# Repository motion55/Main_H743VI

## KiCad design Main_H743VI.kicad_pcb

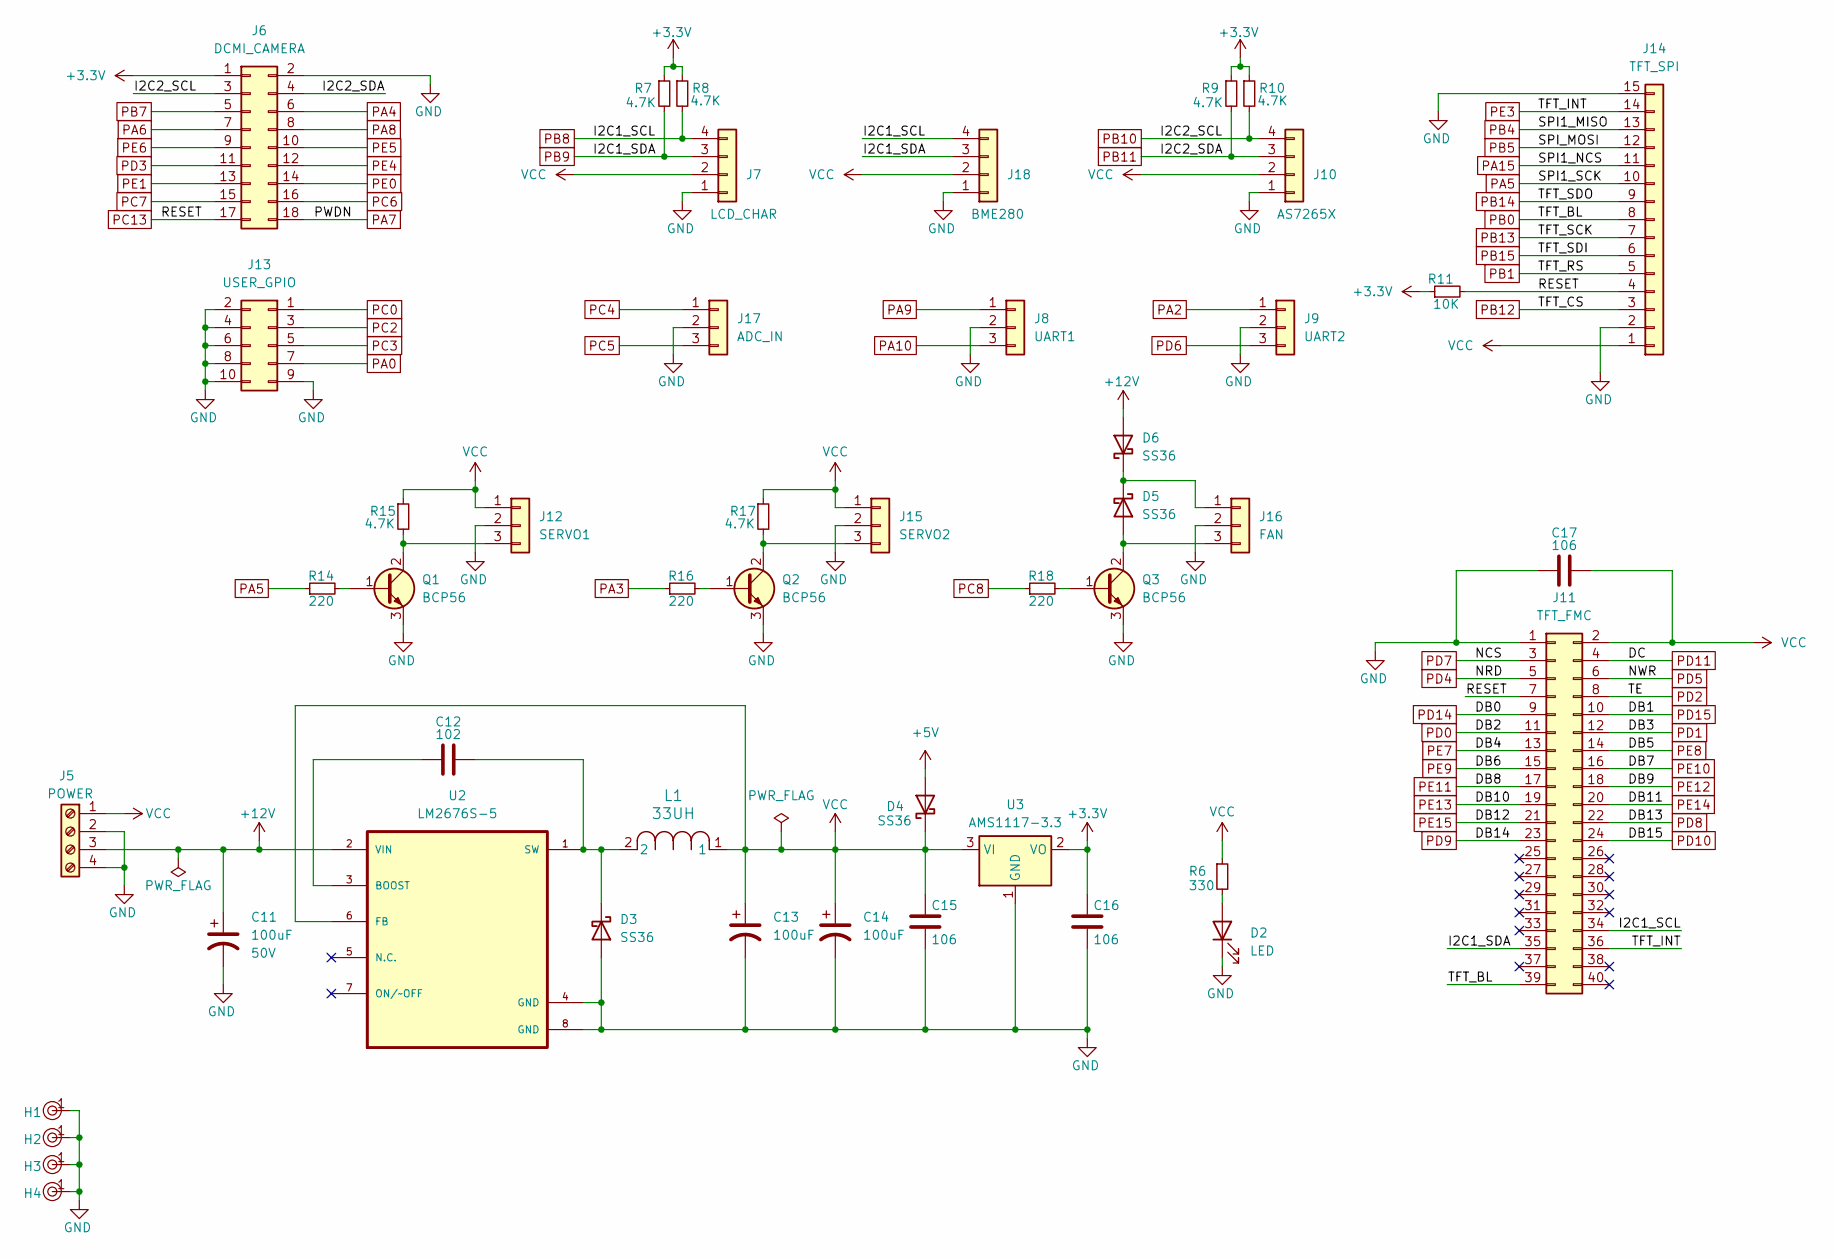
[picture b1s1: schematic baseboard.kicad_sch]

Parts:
C11: 100uF; CP_Radial_D8.0mm_P5.00mm; Tolerance 100%; Voltage 50V
C12: 102; C_0603_1608Metric_Pad1.08x0.95mm_HandSolder
C13, C14: 100uF; CP_Radial_D8.0mm_P5.00mm
C15, C16, C17: 106; C_0805_2012Metric_Pad1.18x1.45mm_HandSolder
D2: LED; LED_0805_2012Metric_Pad1.15x1.40mm_HandSolder
D3, D4, D5, D6: SS36; D_SMA
H1, H2, H3, H4: Hole, 3mm
J5: POWER; TerminalBlock_MaiXu_MX126-5.0-04P_1x04_P5.00mm
J6: DCMI_CAMERA; PinSocket_2x09_P2.54mm_Vertical
J7: LCD_CHAR; PinHeader_1x04_P2.54mm_Vertical
J8: UART1; PinHeader_1x03_P2.54mm_Vertical
J9: UART2; PinHeader_1x03_P2.54mm_Vertical
J10: AS7265X; PinHeader_1x04_P2.54mm_Vertical
J11: TFT_FMC; PinHeader_2x20_P2.54mm_Vertical
J12: SERVO1; PinHeader_1x03_P2.54mm_Vertical
J13: USER_GPIO; PinHeader_2x05_P2.54mm_Vertical
J14: TFT_SPI; PinHeader_1x15_P2.54mm_Vertical
J15: SERVO2; PinHeader_1x03_P2.54mm_Vertical
J16: FAN; PinHeader_1x03_P2.54mm_Vertical
J17: ADC_IN; PinHeader_1x03_P2.54mm_Vertical
J18: BME280; PinHeader_1x04_P2.54mm_Vertical
L1: 33UH; L_SMD,8x8mm
Q1, Q2, Q3: BCP56; SOT-223-3_TabPin2
R6: 330; R_0805_2012Metric_Pad1.20x1.40mm_HandSolder
R7, R8, R9, R10, R15, R17: 4.7K; R_0805_2012Metric_Pad1.20x1.40mm_HandSolder
R11: 10K; R_0805_2012Metric_Pad1.20x1.40mm_HandSolder
R14, R16, R18: 220; R_0805_2012Metric_Pad1.20x1.40mm_HandSolder
U2: LM2676S-5; TO127P1435X464-8N
U3: AMS1117-3.3; SOT-223-3_TabPin2

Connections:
+3.3V: C16.1, J6.1, R7.1, R8.1, R9.1, R10.1, R11.1, U3.2 (VO); also elsewhere on the board
+5V: D4.2 (A); also elsewhere on the board
+12V: C11.1, D6.2 (A), J5.3, U2.2 (VIN)
GND: C11.2, C13.2, C14.2, C15.2, C16.2, C17.1, D2.1 (K), D3.2 (A), H1.1, H2.1, H3.1, H4.1, J5.2, J5.4, J6.2, J7.1, J8.2, J9.2, J10.1, J11.1, J12.2, J13.2, J13.4, J13.6, J13.8, J13.9, J13.10, J14.2, J14.15, J15.2, J16.2, J17.2, J18.1, Q1.3 (E), Q2.3 (E), Q3.3 (E), U2.4 (GND), U2.8 (GND), U3.1 (GND); also elsewhere on the board
unnamed: D2.2 (A), R6.2
unnamed: C12.2, D3.1 (K), L1.2, U2.1 (SW)
unnamed: D5.2 (A), J16.3, Q3.2 (C)
unnamed: D5.1 (K), D6.1 (K), J16.1
unnamed: J12.3, Q1.2 (C), R15.2
unnamed: J15.3, Q2.2 (C), R17.2
unnamed: Q1.1 (B), R14.2
unnamed: Q2.1 (B), R16.2
unnamed: Q3.1 (B), R18.2
unnamed: C12.1, U2.3 (BOOST)
PA0: J13.7; also elsewhere on the board
PA2: J9.1; also elsewhere on the board
PA3: R16.1; also elsewhere on the board
PA4: J6.6; also elsewhere on the board
PA5: J14.10, R14.1; also elsewhere on the board
PA6: J6.7; also elsewhere on the board
PA7: J6.18; also elsewhere on the board
PA8: J6.8; also elsewhere on the board
PA9: J8.1; also elsewhere on the board
PA10: J8.3; also elsewhere on the board
PA15: J14.11; also elsewhere on the board
PB0: J11.39, J14.8; also elsewhere on the board
PB1: J14.5; also elsewhere on the board
PB4: J14.13; also elsewhere on the board
PB5: J14.12; also elsewhere on the board
PB7: J6.5; also elsewhere on the board
PB8: J7.4, J11.34, J18.4, R8.2; also elsewhere on the board
PB9: J7.3, J11.35, J18.3, R7.2; also elsewhere on the board
PB10: J6.3, J10.4, R10.2; also elsewhere on the board
PB11: J6.4, J10.3, R9.2; also elsewhere on the board
PB12: J14.3; also elsewhere on the board
PB13: J14.7; also elsewhere on the board
PB14: J14.9; also elsewhere on the board
PB15: J14.6; also elsewhere on the board
PC0: J13.1; also elsewhere on the board
PC2: J13.3; also elsewhere on the board
PC3: J13.5; also elsewhere on the board
PC4: J17.1; also elsewhere on the board
PC5: J17.3; also elsewhere on the board
PC6: J6.16; also elsewhere on the board
PC7: J6.15; also elsewhere on the board
PC8: R18.1; also elsewhere on the board
PC13: J6.17, J11.7, J14.4, R11.2; also elsewhere on the board
PD0: J11.11; also elsewhere on the board
PD1: J11.12; also elsewhere on the board
PD2: J11.8; also elsewhere on the board
PD3: J6.11; also elsewhere on the board
PD4: J11.5; also elsewhere on the board
PD5: J11.6; also elsewhere on the board
PD6: J9.3; also elsewhere on the board
PD7: J11.3; also elsewhere on the board
PD8: J11.22; also elsewhere on the board
PD9: J11.23; also elsewhere on the board
PD10: J11.24; also elsewhere on the board
PD11: J11.4; also elsewhere on the board
PD14: J11.9; also elsewhere on the board
PD15: J11.10; also elsewhere on the board
PE0: J6.14; also elsewhere on the board
PE1: J6.13; also elsewhere on the board
PE3: J11.36, J14.14; also elsewhere on the board
PE4: J6.12; also elsewhere on the board
PE5: J6.10; also elsewhere on the board
PE6: J6.9; also elsewhere on the board
PE7: J11.13; also elsewhere on the board
PE8: J11.14; also elsewhere on the board
PE9: J11.15; also elsewhere on the board
PE10: J11.16; also elsewhere on the board
PE11: J11.17; also elsewhere on the board
PE12: J11.18; also elsewhere on the board
PE13: J11.19; also elsewhere on the board
PE14: J11.20; also elsewhere on the board
PE15: J11.21; also elsewhere on the board
VCC: C13.1, C14.1, C15.1, C17.2, D4.1 (K), J5.1, J7.2, J10.2, J11.2, J12.1, J14.1, J15.1, J18.2, L1.1, R6.1, R15.1, R17.1, U2.6 (FB), U3.3 (VI)

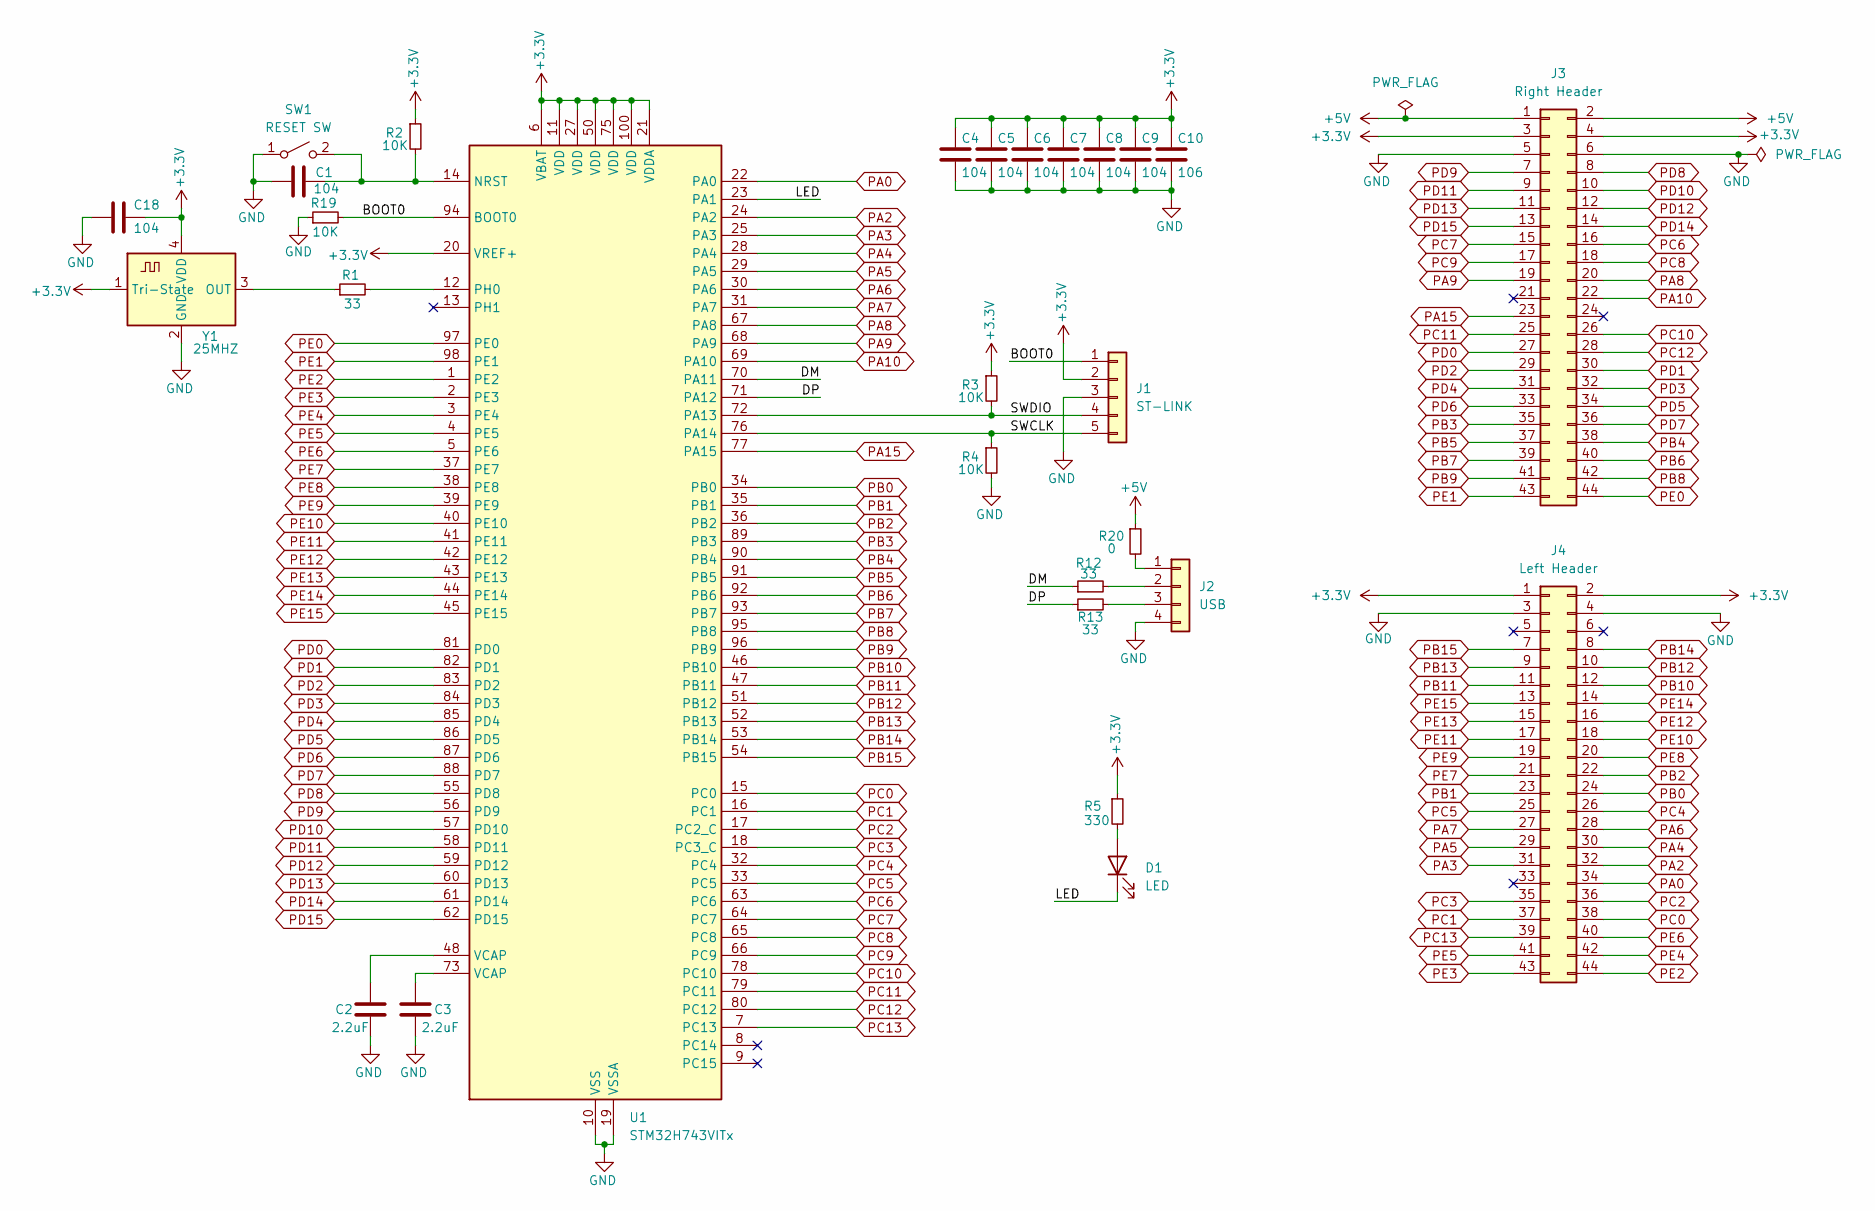
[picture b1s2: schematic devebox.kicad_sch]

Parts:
C1, C4, C5, C6, C7, C8, C9, C18: 104; C_0603_1608Metric_Pad1.08x0.95mm_HandSolder
C2, C3: 2.2uF; C_0805_2012Metric_Pad1.18x1.45mm_HandSolder
C10: 106; C_0603_1608Metric_Pad1.08x0.95mm_HandSolder
D1: LED; LED_0805_2012Metric_Pad1.15x1.40mm_HandSolder
J1: ST-LINK; PinHeader_1x05_P2.54mm_Vertical
J2: USB; PinHeader_1x04_P2.54mm_Vertical
J3: Right Header; PinHeader_2x22_P2.54mm_Vertical
J4: Left Header; PinHeader_2x22_P2.54mm_Vertical
R1, R12, R13: 33; R_0805_2012Metric_Pad1.20x1.40mm_HandSolder
R2, R3, R4, R19: 10K; R_0805_2012Metric_Pad1.20x1.40mm_HandSolder
R5: 330; R_0805_2012Metric_Pad1.20x1.40mm_HandSolder
R20: 0; R_0805_2012Metric_Pad1.20x1.40mm_HandSolder
SW1: RESET SW; SW_PUSH_6mm_H4.3mm
U1: STM32H743VITx; LQFP-100_14x14mm_P0.5mm
Y1: 25MHZ; Oscillator_SMD_Abracon_ASV-4Pin_7.0x5.1mm_HandSoldering

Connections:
+3.3V: C4.1, C5.1, C6.1, C7.1, C8.1, C9.1, C10.1, C18.1, J1.2, J3.3, J3.4, J4.1, J4.2, R2.1, R3.1, R5.1, U1.6 (VBAT), U1.11 (VDD), U1.20 (VREF+), U1.21 (VDDA), U1.27 (VDD), U1.50 (VDD), U1.75 (VDD), U1.100 (VDD), Y1.1 (Tri-State), Y1.4 (VDD); also elsewhere on the board
+5V: J3.1, J3.2, R20.1; also elsewhere on the board
/DEVEBOX/BOOT0: J1.1, R19.2, U1.94 (BOOT0)
/DEVEBOX/DM: R12.1, U1.70 (PA11)
/DEVEBOX/DP: R13.1, U1.71 (PA12)
/DEVEBOX/LED: D1.1 (K), U1.23 (PA1)
/DEVEBOX/SWCLK: J1.5, R4.1, U1.76 (PA14)
/DEVEBOX/SWDIO: J1.4, R3.2, U1.72 (PA13)
GND: C1.2, C2.2, C3.2, C4.2, C5.2, C6.2, C7.2, C8.2, C9.2, C10.2, C18.2, J1.3, J2.4, J3.5, J3.6, J4.3, J4.4, R4.2, R19.1, SW1.1 (A), U1.10 (VSS), U1.19 (VSSA), U1.26 (VSS), U1.49 (VSS), U1.74 (VSS), U1.99 (VSS), Y1.2 (GND); also elsewhere on the board
unnamed: C2.1, U1.48 (VCAP)
unnamed: C3.1, U1.73 (VCAP)
unnamed: D1.2 (A), R5.2
unnamed: J2.1, R20.2
unnamed: J2.2, R12.2
unnamed: J2.3, R13.2
unnamed: C1.1, R2.2, SW1.2 (B), U1.14 (NRST)
unnamed: R1.2, U1.12 (PH0)
unnamed: R1.1, Y1.3 (OUT)
PA0: J4.34, U1.22 (PA0); also elsewhere on the board
PA2: J4.32, U1.24 (PA2); also elsewhere on the board
PA3: J4.31, U1.25 (PA3); also elsewhere on the board
PA4: J4.30, U1.28 (PA4); also elsewhere on the board
PA5: J4.29, U1.29 (PA5); also elsewhere on the board
PA6: J4.28, U1.30 (PA6); also elsewhere on the board
PA7: J4.27, U1.31 (PA7); also elsewhere on the board
PA8: J3.20, U1.67 (PA8); also elsewhere on the board
PA9: J3.19, U1.68 (PA9); also elsewhere on the board
PA10: J3.22, U1.69 (PA10); also elsewhere on the board
PA15: J3.23, U1.77 (PA15); also elsewhere on the board
PB0: J4.24, U1.34 (PB0); also elsewhere on the board
PB1: J4.23, U1.35 (PB1); also elsewhere on the board
PB2: J4.22, U1.36 (PB2)
PB3: J3.35, U1.89 (PB3)
PB4: J3.38, U1.90 (PB4); also elsewhere on the board
PB5: J3.37, U1.91 (PB5); also elsewhere on the board
PB6: J3.40, U1.92 (PB6)
PB7: J3.39, U1.93 (PB7); also elsewhere on the board
PB8: J3.42, U1.95 (PB8); also elsewhere on the board
PB9: J3.41, U1.96 (PB9); also elsewhere on the board
PB10: J4.12, U1.46 (PB10); also elsewhere on the board
PB11: J4.11, U1.47 (PB11); also elsewhere on the board
PB12: J4.10, U1.51 (PB12); also elsewhere on the board
PB13: J4.9, U1.52 (PB13); also elsewhere on the board
PB14: J4.8, U1.53 (PB14); also elsewhere on the board
PB15: J4.7, U1.54 (PB15); also elsewhere on the board
PC0: J4.38, U1.15 (PC0); also elsewhere on the board
PC1: J4.37, U1.16 (PC1)
PC2: J4.36, U1.17 (PC2_C); also elsewhere on the board
PC3: J4.35, U1.18 (PC3_C); also elsewhere on the board
PC4: J4.26, U1.32 (PC4); also elsewhere on the board
PC5: J4.25, U1.33 (PC5); also elsewhere on the board
PC6: J3.16, U1.63 (PC6); also elsewhere on the board
PC7: J3.15, U1.64 (PC7); also elsewhere on the board
PC8: J3.18, U1.65 (PC8); also elsewhere on the board
PC9: J3.17, U1.66 (PC9)
PC10: J3.26, U1.78 (PC10)
PC11: J3.25, U1.79 (PC11)
PC12: J3.28, U1.80 (PC12)
PC13: J4.39, U1.7 (PC13); also elsewhere on the board
PD0: J3.27, U1.81 (PD0); also elsewhere on the board
PD1: J3.30, U1.82 (PD1); also elsewhere on the board
PD2: J3.29, U1.83 (PD2); also elsewhere on the board
PD3: J3.32, U1.84 (PD3); also elsewhere on the board
PD4: J3.31, U1.85 (PD4); also elsewhere on the board
PD5: J3.34, U1.86 (PD5); also elsewhere on the board
PD6: J3.33, U1.87 (PD6); also elsewhere on the board
PD7: J3.36, U1.88 (PD7); also elsewhere on the board
PD8: J3.8, U1.55 (PD8); also elsewhere on the board
PD9: J3.7, U1.56 (PD9); also elsewhere on the board
PD10: J3.10, U1.57 (PD10); also elsewhere on the board
PD11: J3.9, U1.58 (PD11); also elsewhere on the board
PD12: J3.12, U1.59 (PD12)
PD13: J3.11, U1.60 (PD13)
PD14: J3.14, U1.61 (PD14); also elsewhere on the board
PD15: J3.13, U1.62 (PD15); also elsewhere on the board
PE0: J3.44, U1.97 (PE0); also elsewhere on the board
PE1: J3.43, U1.98 (PE1); also elsewhere on the board
PE2: J4.44, U1.1 (PE2)
PE3: J4.43, U1.2 (PE3); also elsewhere on the board
PE4: J4.42, U1.3 (PE4); also elsewhere on the board
PE5: J4.41, U1.4 (PE5); also elsewhere on the board
PE6: J4.40, U1.5 (PE6); also elsewhere on the board
PE7: J4.21, U1.37 (PE7); also elsewhere on the board
PE8: J4.20, U1.38 (PE8); also elsewhere on the board
PE9: J4.19, U1.39 (PE9); also elsewhere on the board
PE10: J4.18, U1.40 (PE10); also elsewhere on the board
PE11: J4.17, U1.41 (PE11); also elsewhere on the board
PE12: J4.16, U1.42 (PE12); also elsewhere on the board
PE13: J4.15, U1.43 (PE13); also elsewhere on the board
PE14: J4.14, U1.44 (PE14); also elsewhere on the board
PE15: J4.13, U1.45 (PE15); also elsewhere on the board

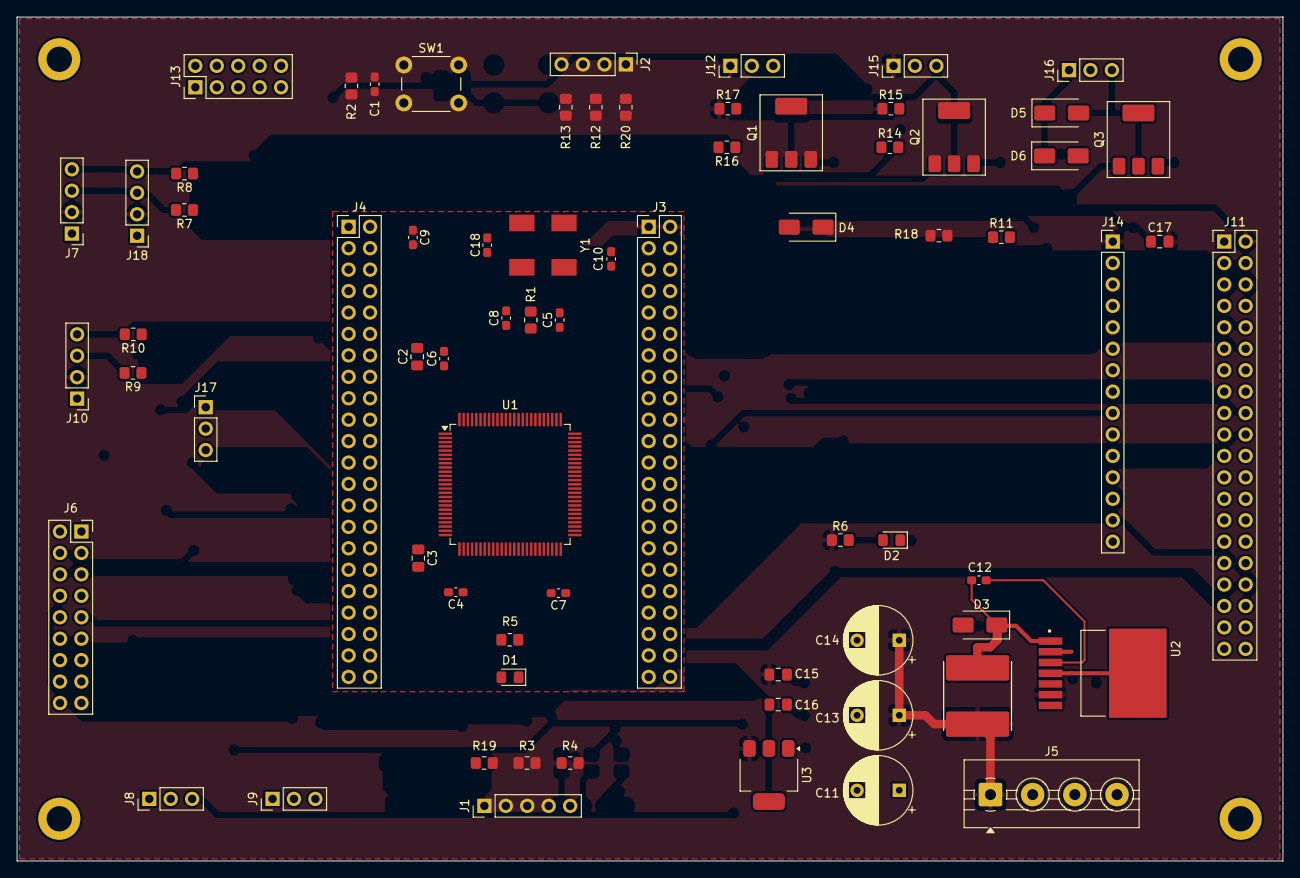
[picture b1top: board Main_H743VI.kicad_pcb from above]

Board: 4 copper layers, 150.0 x 100.0 mm, 75 parts (0 on the bottom side), 103 nets.

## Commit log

2025-03-23 initial
2025-03-24 snapshot
2025-03-24 Place all parts and resize board
2025-03-25 remove zip backups from repo
2025-03-26 add servos and fan outputs
2025-03-27 move servo connector closer to power supply
2025-03-27 change transistors from MMBT2222A to BCP56
2025-03-27 move diode closer to +5V
2025-03-28 flipped camera connector
2025-03-28 snapshotprior to autorout
2025-03-28 end of day snapshot
2025-03-29 Reassign pin (PA5 to PB3) to dix duplicate PA5
